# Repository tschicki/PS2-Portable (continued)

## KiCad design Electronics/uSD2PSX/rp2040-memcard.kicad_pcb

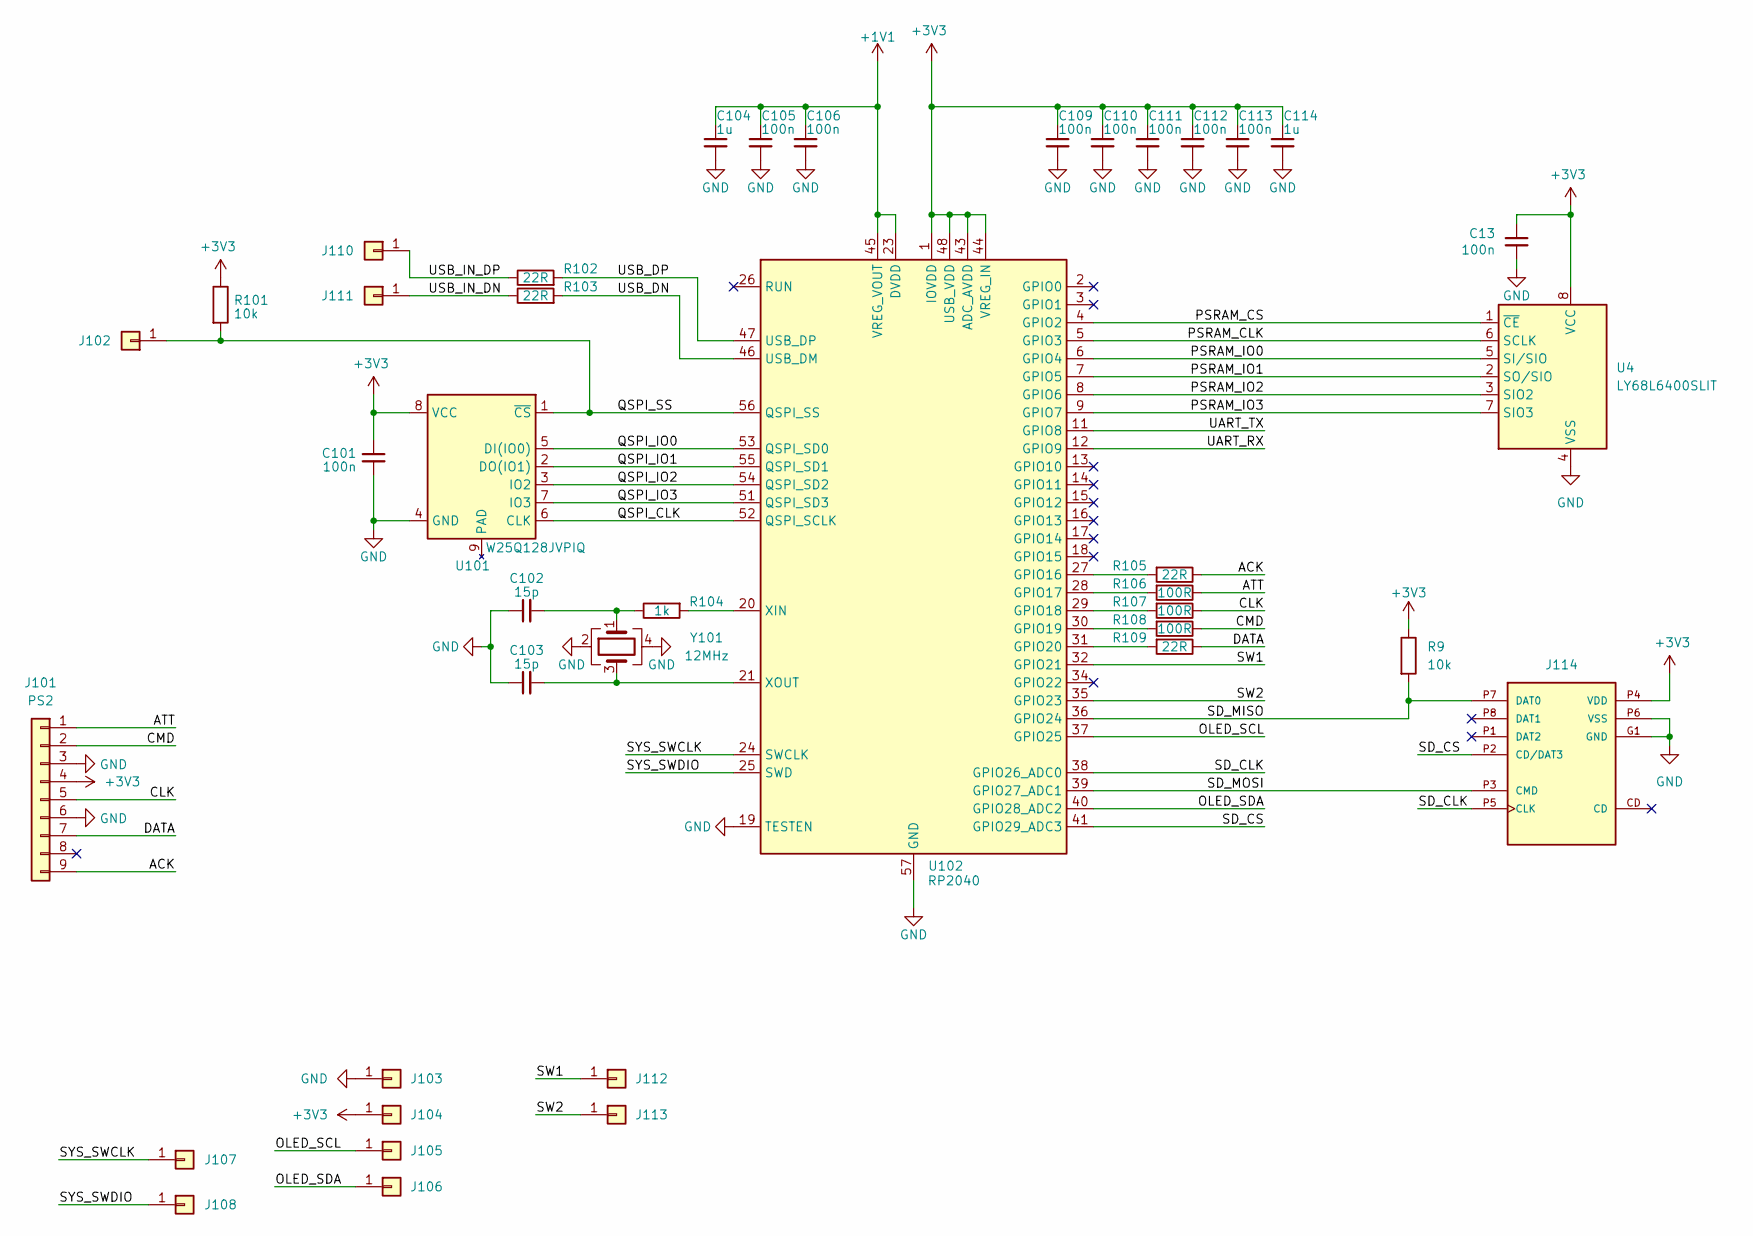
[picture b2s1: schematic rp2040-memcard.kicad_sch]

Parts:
C13, C101, C105, C106, C109, C110, C111, C112, C113: 100n; C_0402_1005Metric; Part Number CC0402KRX7R7BB104
C102, C103: 15p; C_0402_1005Metric; Part Number CC0402JRNPO9BN150
C104, C114: 1u; C_0603_1608Metric; Part Number CC0603KRX7R7BB105
J101: PS2; SD_Pins
J102: BSEL; TestPoint_Pad_D1.0mm
J103, J112: GND; TestPoint_Pad_D1.0mm
J104, J113: 3V3; TestPoint_Pad_D1.0mm
J105: SCL; TestPoint_Pad_D1.0mm
J106: SDA; TestPoint_Pad_D1.0mm
J107: SWC; TestPoint_Pad_D1.0mm
J108: SWD; TestPoint_Pad_D1.0mm
J110: DP; TestPoint_Pad_D1.0mm
J111: DN; TestPoint_Pad_D1.0mm
J114: MEM2085-00-115-00-A_REV0.2; GCT_MEM2085-00-115-00-A_REV0.2; Part Number MEM2085-00-115-00-A
R9, R101: 10k; R_0402_1005Metric; Part Number RC0402JR-0710KL
R102, R103, R105, R109: 22R; R_0402_1005Metric; Part Number RC0402FR-0722RL
R104: 1k; R_0402_1005Metric; Part Number RC0402FR-071KL
R106, R107, R108: 100R; R_0402_1005Metric; Part Number RC0402JR-07100RL
U4: LY68L6400SLIT; IC_W25Q16JVUXIQ_TR; Part Number APS6404L-3SQR-ZR; LCSC C261881
U101: W25Q128JVPIQ; WSON-8-1EP_6x5mm_P1.27mm_EP3.4x4.3mm; Part Number W25Q128JVPIQ
U102: RP2040; QFN-56-1EP_7x7mm_P0.4mm_EP3.2x3.2mm; Part Number RP2040
Y101: 12MHz; Crystal_SMD_3225-4Pin_3.2x2.5mm; Part Number FL1200112

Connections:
+1V1: C104.1, C105.1, C106.1, U102.23 (DVDD), U102.45 (VREG_VOUT), U102.50 (DVDD)
+3V3: C13.1, C101.1, C109.1, C110.1, C111.1, C112.1, C113.1, C114.1, J101.4, J104.1, J114.P4 (VDD), R9.1, R101.1, U4.8 (VCC), U101.8 (VCC), U102.1 (IOVDD), U102.10 (IOVDD), U102.22 (IOVDD), U102.33 (IOVDD), U102.42 (IOVDD), U102.43 (ADC_AVDD), U102.44 (VREG_IN), U102.48 (USB_VDD), U102.49 (IOVDD)
/ACK: J101.9, R105.1
/ATT: J101.1, R106.1
/CLK: J101.5, R107.1
/CMD: J101.2, R108.1
/DATA: J101.7, R109.1
/OLED_SCL: J105.1, U102.37 (GPIO25)
/OLED_SDA: J106.1, U102.40 (GPIO28_ADC2)
/PSRAM_CLK: U4.6 (SCLK), U102.5 (GPIO3)
/PSRAM_CS: U4.1 (~CE), U102.4 (GPIO2)
/PSRAM_IO0: U4.5 (SI/SIO), U102.6 (GPIO4)
/PSRAM_IO1: U4.2 (SO/SIO), U102.7 (GPIO5)
/PSRAM_IO2: U4.3 (SIO2), U102.8 (GPIO6)
/PSRAM_IO3: U4.7 (SIO3), U102.9 (GPIO7)
/QSPI_CLK: U101.6 (CLK), U102.52 (QSPI_SCLK)
/QSPI_IO0: U101.5 (DI(IO0)), U102.53 (QSPI_SD0)
/QSPI_IO1: U101.2 (DO(IO1)), U102.55 (QSPI_SD1)
/QSPI_IO2: U101.3 (IO2), U102.54 (QSPI_SD2)
/QSPI_IO3: U101.7 (IO3), U102.51 (QSPI_SD3)
/QSPI_SS: J102.1, R101.2, U101.1 (~CS), U102.56 (QSPI_SS)
/SD_CLK: J114.P5 (CLK), U102.38 (GPIO26_ADC0)
/SD_CS: J114.P2 (CD/DAT3), U102.41 (GPIO29_ADC3)
/SD_MISO: J114.P7 (DAT0), R9.2, U102.36 (GPIO24)
/SD_MOSI: J114.P3 (CMD), U102.39 (GPIO27_ADC1)
/SW1: J112.1, U102.32 (GPIO21)
/SW2: J113.1, U102.35 (GPIO23)
/SYS_SWCLK: J107.1, U102.24 (SWCLK)
/SYS_SWDIO: J108.1, U102.25 (SWD)
/UART_RX: U102.12 (GPIO9)
/UART_TX: U102.11 (GPIO8)
/USB_DN: R103.2, U102.46 (USB_DM)
/USB_DP: R102.2, U102.47 (USB_DP)
/USB_IN_DN: J111.1, R103.1
/USB_IN_DP: J110.1, R102.1
GND: C13.2, C101.2, C102.1, C103.1, C104.2, C105.2, C106.2, C109.2, C110.2, C111.2, C112.2, C113.2, C114.2, J101.3, J101.6, J103.1, J114.G1 (GND), J114.G2 (GND__1), J114.G3 (GND__2), J114.G4 (GND__3), J114.G5 (GND__4), J114.G6 (GND__5), J114.G7 (GND__6), J114.G8 (GND__7), J114.G9 (GND__8), J114.G10 (GND__9), J114.P6 (VSS), U4.4 (VSS), U101.4 (GND), U102.19 (TESTEN), U102.57 (GND), Y101.2, Y101.4
unnamed: C102.2, R104.1, Y101.1
unnamed: R105.2, U102.27 (GPIO16)
unnamed: R106.2, U102.28 (GPIO17)
unnamed: R107.2, U102.29 (GPIO18)
unnamed: R108.2, U102.30 (GPIO19)
unnamed: R109.2, U102.31 (GPIO20)
unnamed: R104.2, U102.20 (XIN)
unnamed: C103.2, U102.21 (XOUT), Y101.3

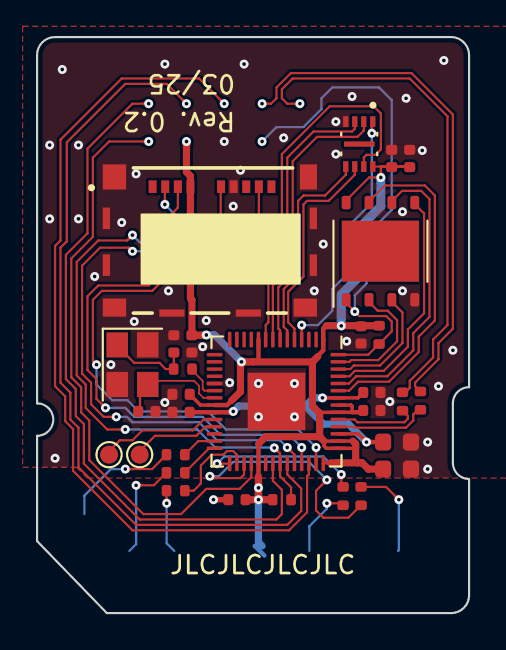
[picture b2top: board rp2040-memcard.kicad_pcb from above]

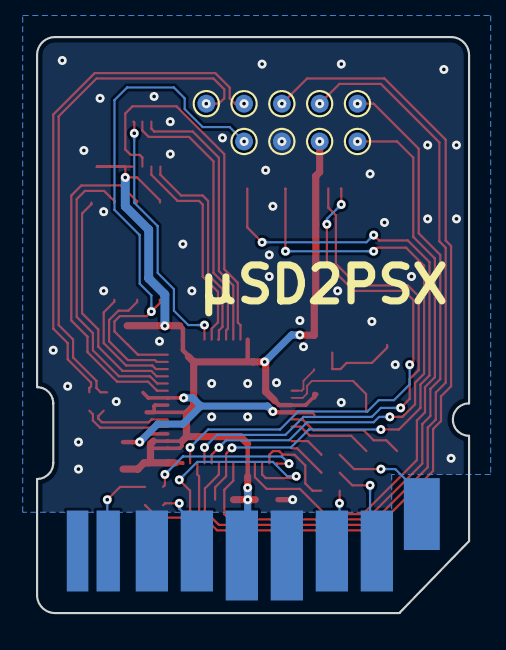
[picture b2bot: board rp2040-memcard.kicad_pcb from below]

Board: 2 copper layers, 24.0 x 32.0 mm, 40 parts (10 on the bottom side), 42 nets.

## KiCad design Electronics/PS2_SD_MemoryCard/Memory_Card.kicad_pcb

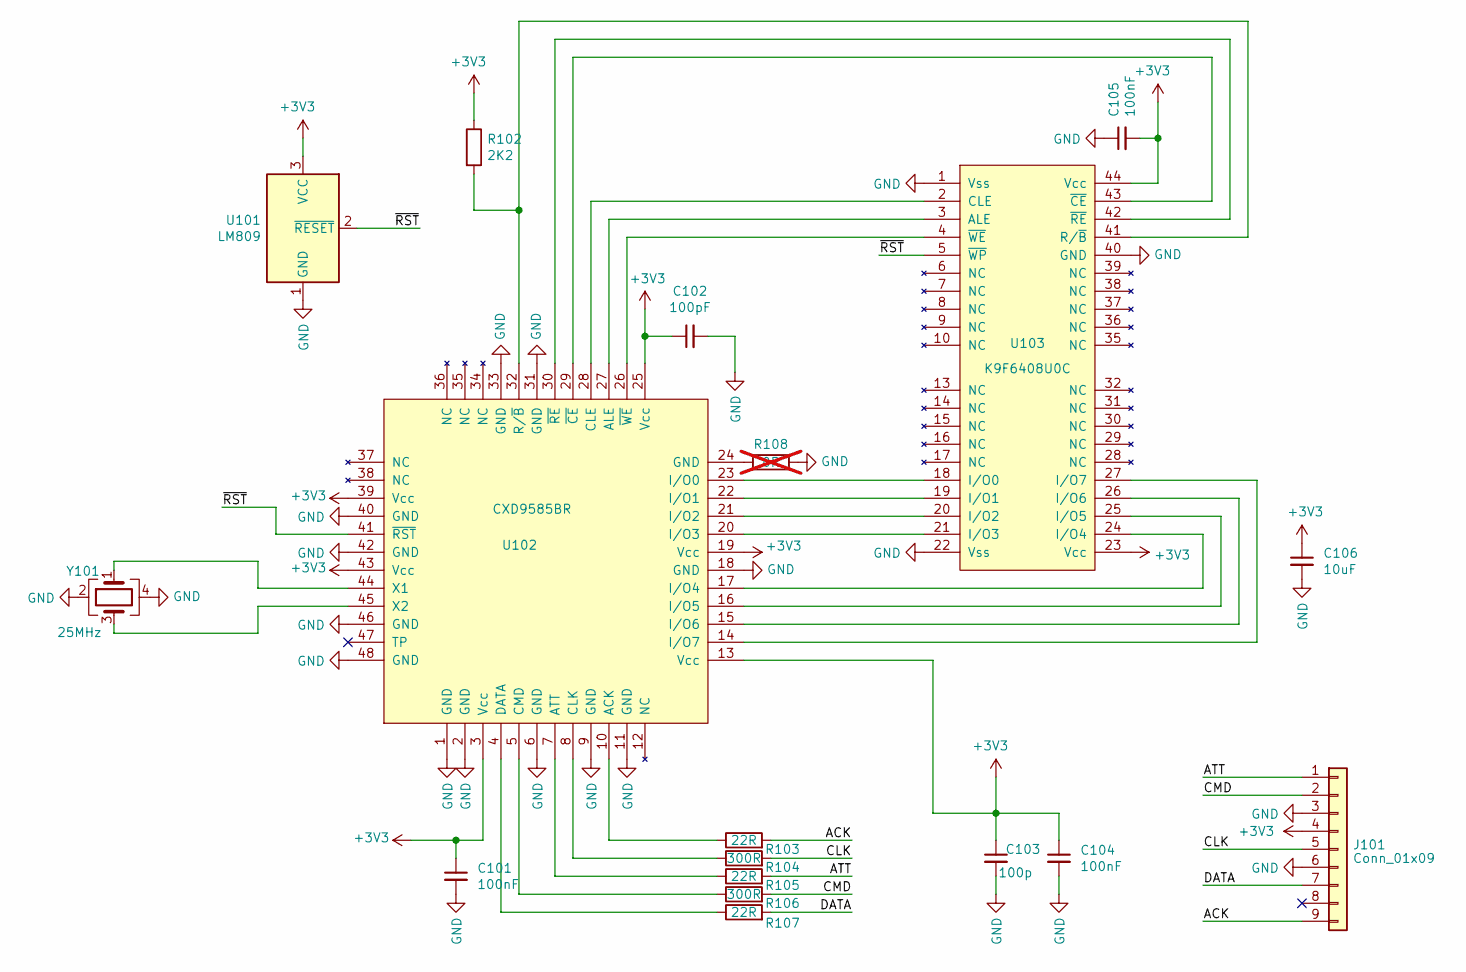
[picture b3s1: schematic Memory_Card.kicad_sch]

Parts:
C101, C104, C105: 100nF; C_0402_1005Metric; Part Number CC0402KRX7R7BB104
C102: 100pF; C_0402_1005Metric; Part Number CC0402KRX7R9BB101
C103: 100p; C_0402_1005Metric; Part Number CC0402KRX7R9BB101
C106: 10uF; C_0805_2012Metric; Part Number 885012107014
J101: Conn_01x09; SD_Pins
R102: 2K2; R_0402_1005Metric; Part Number RC0402FR-072K2L
R103, R105, R107: 22R; R_0402_1005Metric; Part Number RC0402FR-0722RL
R104, R106: 300R; R_0402_1005Metric; Part Number RC0402JR-07300RL
R108: 0R; R_0402_1005Metric; Part Number RC0402JR-130RL; not fitted
U101: LM809; SOT-23; Part Number LM809M3-2.63/NOPB
U102: CXD9585BR; LQFP-48_7x7mm_P0.5mm; Part Number Get off board
U103: K9F6408U0C; TSOP-II-44_10.16x18.41mm_P0.8mm; Part Number Get off board
Y101: 25MHz; Crystal_SMD_2016-4Pin_2.0x1.6mm; Part Number 402F2501XIAR

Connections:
+3V3: C101.1, C102.1, C103.1, C104.1, C105.2, C106.1, J101.4, R102.1, U101.3 (VCC), U102.3 (Vcc), U102.13 (Vcc), U102.19 (Vcc), U102.25 (Vcc), U102.39 (Vcc), U102.43 (Vcc), U103.23 (Vcc), U103.44 (Vcc)
/ACK: J101.9, R103.2
/ATT: J101.1, R105.2
/CLK: J101.5, R104.2
/CMD: J101.2, R106.2
/DATA: J101.7, R107.2
/~RST: U101.2 (~RESET), U102.41 (~RST), U103.5 (~WP)
GND: C101.2, C102.2, C103.2, C104.2, C105.1, C106.2, J101.3, J101.6, R108.2, U101.1 (GND), U102.1 (GND), U102.2 (GND), U102.6 (GND), U102.9 (GND), U102.11 (GND), U102.18 (GND), U102.31 (GND), U102.33 (GND), U102.40 (GND), U102.42 (GND), U102.46 (GND), U102.48 (GND), U103.1 (Vss), U103.22 (Vss), U103.40 (GND), Y101.2, Y101.4
unnamed: R108.1, U102.24 (GND)
unnamed: R103.1, U102.10 (ACK)
unnamed: U102.27 (ALE), U103.3 (ALE)
unnamed: R105.1, U102.7 (ATT)
unnamed: U102.28 (CLE), U103.2 (CLE)
unnamed: R104.1, U102.8 (CLK)
unnamed: R106.1, U102.5 (CMD)
unnamed: R107.1, U102.4 (DATA)
unnamed: U102.23 (I/O0), U103.18 (I/O0)
unnamed: U102.22 (I/O1), U103.19 (I/O1)
unnamed: U102.21 (I/O2), U103.20 (I/O2)
unnamed: U102.20 (I/O3), U103.21 (I/O3)
unnamed: U102.17 (I/O4), U103.24 (I/O4)
unnamed: U102.16 (I/O5), U103.25 (I/O5)
unnamed: U102.15 (I/O6), U103.26 (I/O6)
unnamed: U102.14 (I/O7), U103.27 (I/O7)
unnamed: R102.2, U102.32 (R/~B), U103.41 (R/~B)
unnamed: U102.44 (X1), Y101.1
unnamed: U102.45 (X2), Y101.3
unnamed: U102.29 (~CE), U103.43 (~CE)
unnamed: U102.30 (~RE), U103.42 (~RE)
unnamed: U102.26 (~WE), U103.4 (~WE)

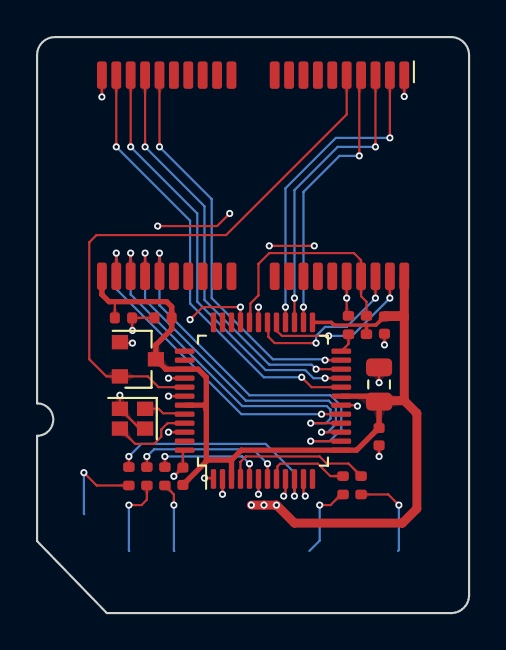
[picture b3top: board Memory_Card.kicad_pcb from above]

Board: 2 copper layers, 24.0 x 32.0 mm, 18 parts (1 on the bottom side), 30 nets.

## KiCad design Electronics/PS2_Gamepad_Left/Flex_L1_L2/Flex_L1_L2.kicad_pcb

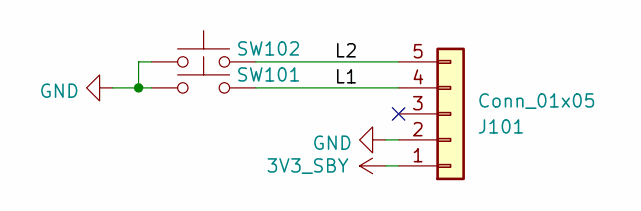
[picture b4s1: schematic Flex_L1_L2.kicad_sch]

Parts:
J101: Conn_01x05; 5034800540_FFC
SW101, SW102: SW; SW_KSC222J_LFS; Part Number KSC222J_LFS

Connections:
3V3_SBY: J101.1
/L1: J101.4, SW101.2
/L2: J101.5, SW102.2
GND: J101.2, SW101.1, SW102.1

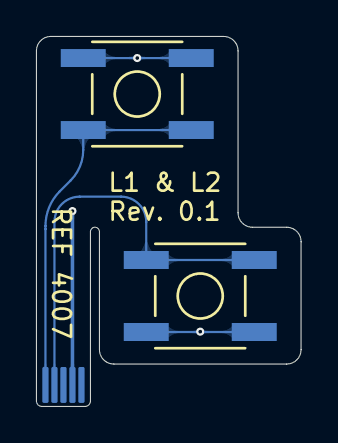
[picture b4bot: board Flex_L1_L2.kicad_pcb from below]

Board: 2 copper layers, 14.7 x 20.6 mm, 3 parts (3 on the bottom side), 3 nets.

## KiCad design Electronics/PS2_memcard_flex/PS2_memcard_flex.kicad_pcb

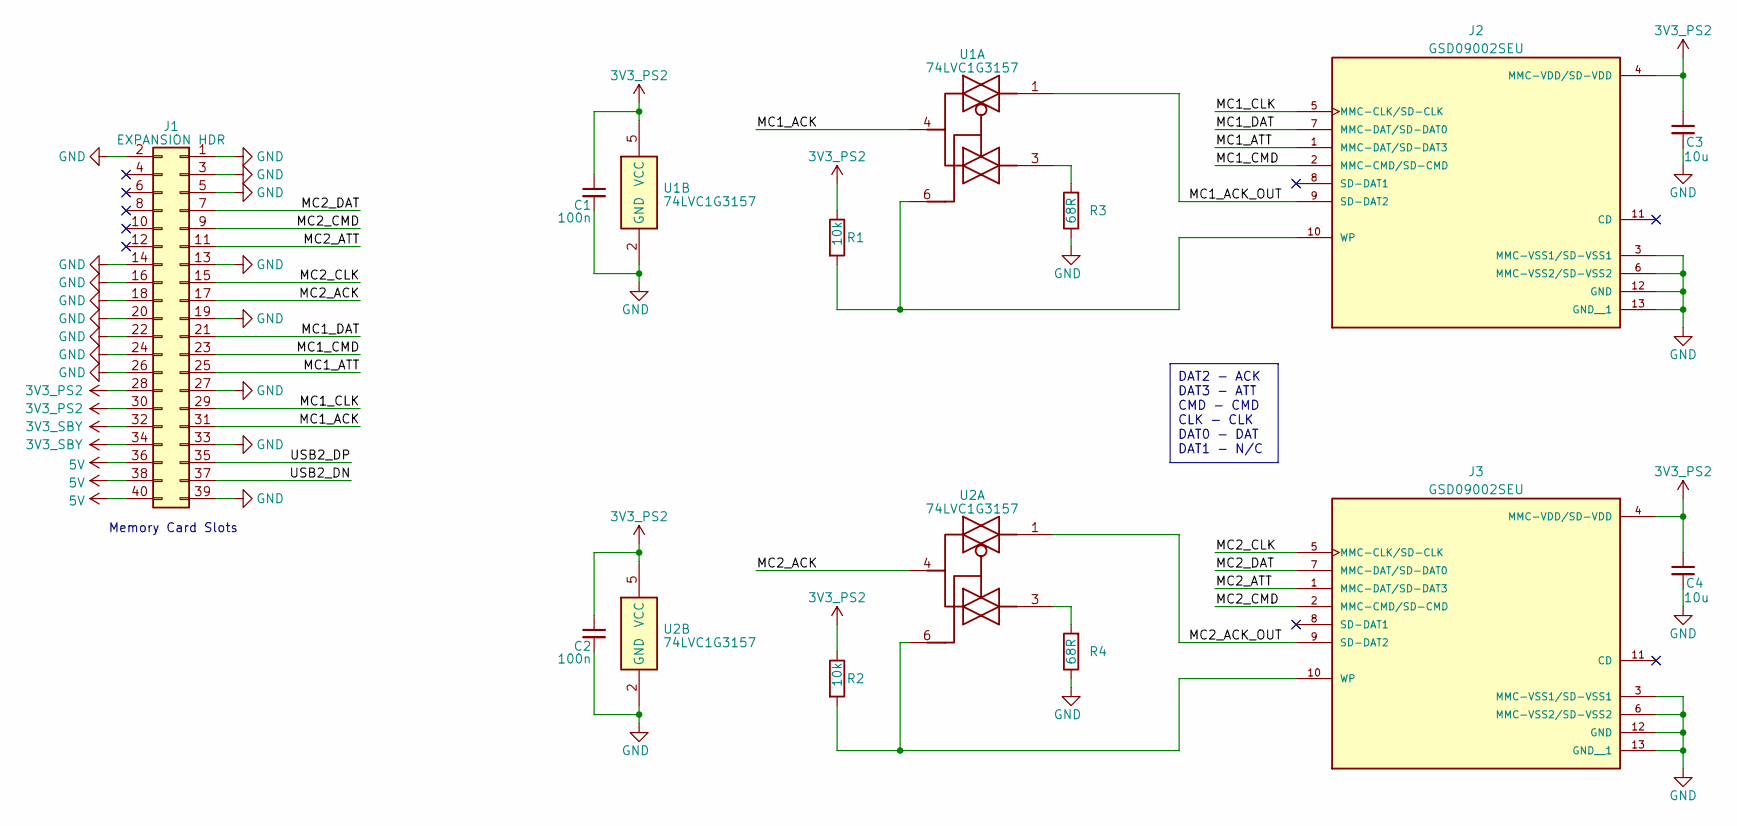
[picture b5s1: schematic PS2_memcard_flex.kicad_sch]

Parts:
C1, C2: 100n; C_0402_1005Metric; Part Number CC0402KRX7R7BB104
C3, C4: 10u; C_0805_2012Metric; Part Number TMK212BBJ106MGHT
J1: EXPANSION HDR; DF40C-40DP-0.4V; Part Number DF40C-40DP-0.4V(51)
J2, J3: GSD09002SEU; AMPHENOL_GSD09002SEU; Part Number GSD09002SEU
R1, R2: 10k; R_0402_1005Metric; Part Number RC0402JR-0710KL
R3, R4: 68R; R_0402_1005Metric; Part Number RC0402FR-0768RL
U1, U2: 74LVC1G3157; SOT-363_SC-70-6; Part Number 74LVC1G3157GW,125

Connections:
3V3_PS2: C1.1, C2.1, C3.1, C4.1, J1.28, J1.30, J2.4 (MMC-VDD/SD-VDD), J3.4 (MMC-VDD/SD-VDD), R1.1, R2.1, U1.5 (VCC), U2.5 (VCC)
3V3_SBY: J1.32, J1.34
5V: J1.36, J1.38, J1.40
/MC1_ACK: J1.31, U1.4
/MC1_ACK_OUT: J2.9 (SD-DAT2), U1.1
/MC1_ATT: J1.25, J2.1 (MMC-DAT/SD-DAT3)
/MC1_CLK: J1.29, J2.5 (MMC-CLK/SD-CLK)
/MC1_CMD: J1.23, J2.2 (MMC-CMD/SD-CMD)
/MC1_DAT: J1.21, J2.7 (MMC-DAT/SD-DAT0)
/MC2_ACK: J1.17, U2.4
/MC2_ACK_OUT: J3.9 (SD-DAT2), U2.1
/MC2_ATT: J1.11, J3.1 (MMC-DAT/SD-DAT3)
/MC2_CLK: J1.15, J3.5 (MMC-CLK/SD-CLK)
/MC2_CMD: J1.9, J3.2 (MMC-CMD/SD-CMD)
/MC2_DAT: J1.7, J3.7 (MMC-DAT/SD-DAT0)
/USB2_DN: J1.37
/USB2_DP: J1.35
GND: C1.2, C2.2, C3.2, C4.2, J1.1, J1.2, J1.3, J1.5, J1.13, J1.14, J1.16, J1.18, J1.19, J1.20, J1.22, J1.24, J1.26, J1.27, J1.33, J1.39, J2.3 (MMC-VSS1/SD-VSS1), J2.6 (MMC-VSS2/SD-VSS2), J2.12 (GND), J2.13 (GND__1), J3.3 (MMC-VSS1/SD-VSS1), J3.6 (MMC-VSS2/SD-VSS2), J3.12 (GND), J3.13 (GND__1), R3.1, R4.1, U1.2 (GND), U2.2 (GND)
unnamed: J2.10 (WP), R1.2, U1.6
unnamed: J3.10 (WP), R2.2, U2.6
unnamed: R3.2, U1.3
unnamed: R4.2, U2.3

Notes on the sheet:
DAT2 - ACK DAT3 - ATT CMD - CMD CLK - CLK DAT0 - DAT DAT1 - N/C
Memory Card Slots

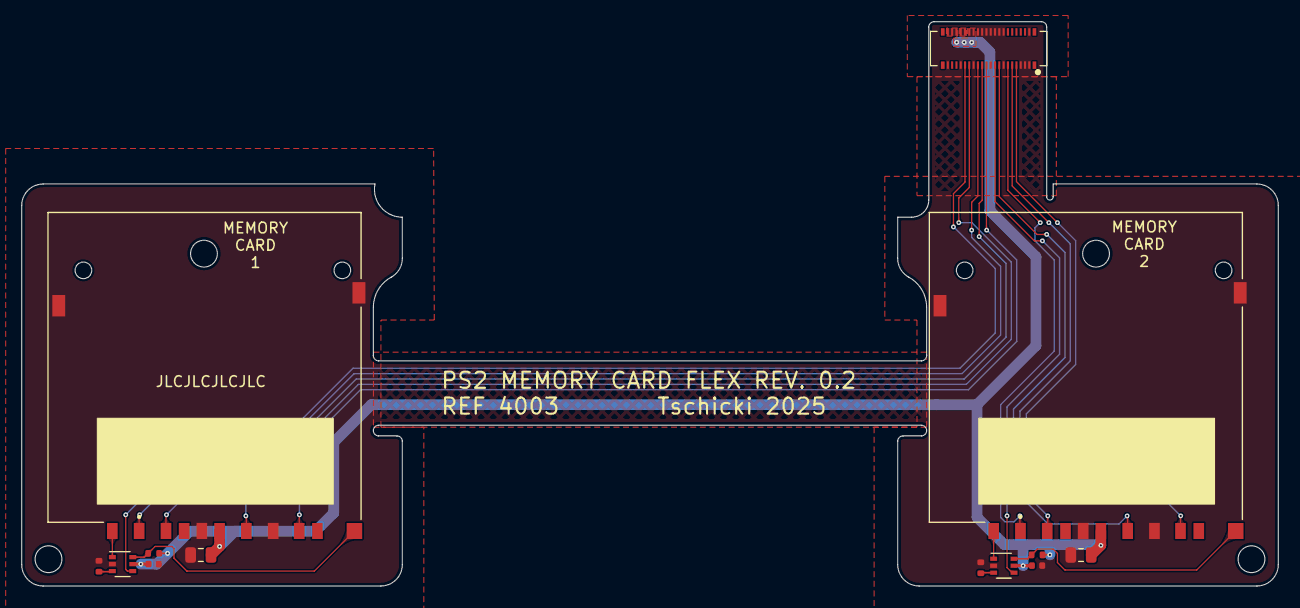
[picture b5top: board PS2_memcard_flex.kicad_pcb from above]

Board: 2 copper layers, 117.2 x 52.6 mm, 13 parts (0 on the bottom side), 20 nets.

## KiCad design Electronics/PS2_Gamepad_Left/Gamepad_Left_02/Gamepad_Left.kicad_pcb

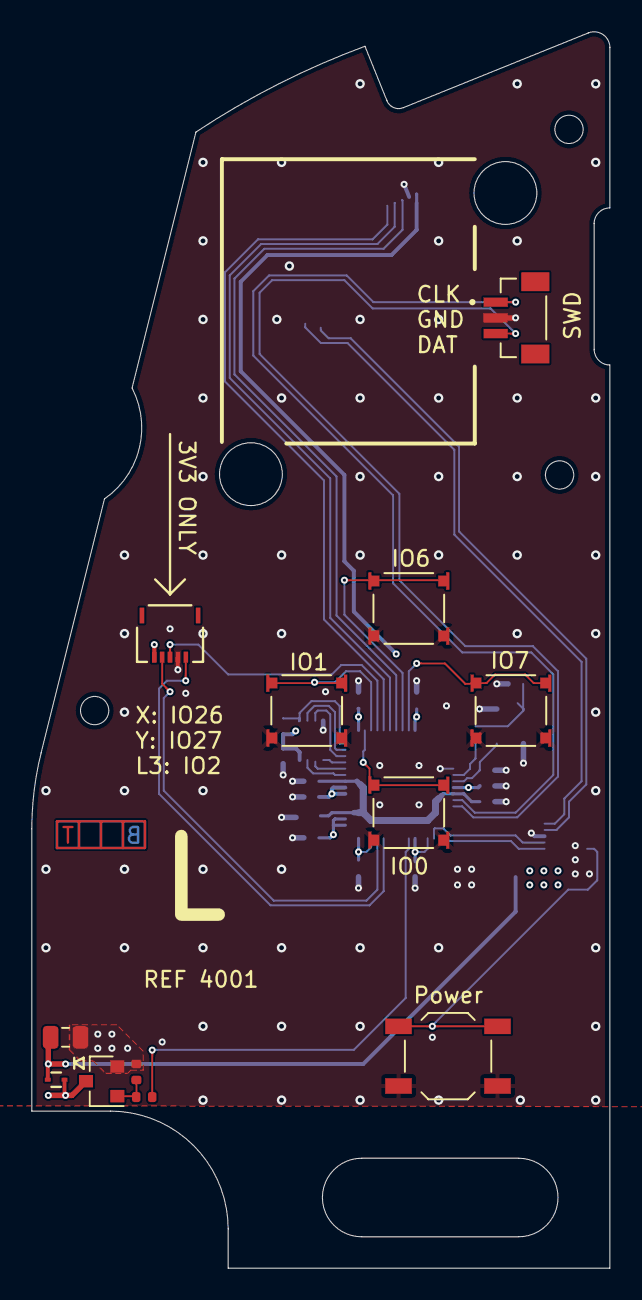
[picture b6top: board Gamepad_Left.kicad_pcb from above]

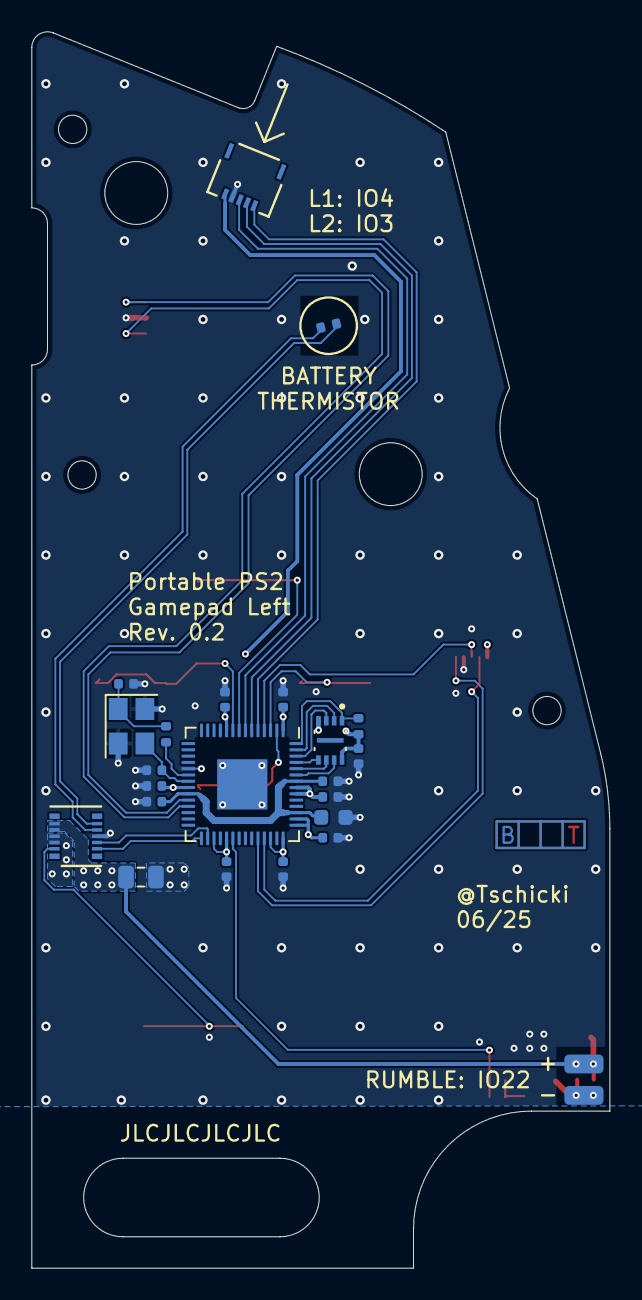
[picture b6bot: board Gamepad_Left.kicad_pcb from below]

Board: 4 copper layers, 36.8 x 78.7 mm, 35 parts (23 on the bottom side), 32 nets.

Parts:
C101, C105, C106, C107, C109, C110, C111, C112, C113, C114: 100n; C_0402_1005Metric
C102, C103: 15p; C_0402_1005Metric
C104: 1u; C_0603_1608Metric
C108, C115: 4u7; C_0805_2012Metric
D101: D_Schottky; SOD-923_0P6X0P85_ONS
J101: DEBUG_SWD; JST_BM03B-SRSS-TB_LF__SN_
J102: GAMEPAD LEFT; DF40C-10DP-0.4V51_HIR
J103, J116: Conn_01x05_MountingPin; CON_5034800540_MOL
J104: Motor; rumble_dual_solder_pad
Q101: BSS138; SOT-23
R101, R103: 10k; R_0402_1005Metric
R102, R104: 1k; R_0402_1005Metric
SW101, SW102, SW103, SW104: SW; SW_TL3315NF100Q
SW114: SW; SW_SPST_TL3342
TH101: 10k/3435K; R_0402_1005Metric
U101: W25Q16JVUXIQ; IC_W25Q16JVUXIQ_TR
U102: RP2040; QFN-56-1EP_7x7mm_P0.4mm_EP3.2x3.2mm
Y101: 12MHz; Crystal_SMD_3225-4Pin_3.2x2.5mm

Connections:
3V3_SBY: C101.1, C107.1, C108.1, C109.1, C110.1, C111.1, C112.1, C113.1, C114.1, C115.1, D101.1 (K), J102.7, J102.9, J103.5, J104.1, J116.5, R101.1, U101.8 (VCC), U102.1 (IOVDD), U102.10 (IOVDD), U102.22 (IOVDD), U102.31 (GPIO20), U102.33 (IOVDD), U102.40 (GPIO28_ADC2), U102.42 (IOVDD), U102.43 (ADC_AVDD), U102.44 (VREG_IN), U102.48 (USB_VDD), U102.49 (IOVDD)
+1V1: C104.1, C105.1, C106.1, U102.23 (DVDD), U102.45 (VREG_VOUT), U102.50 (DVDD)
/AUX_I2C_SCL: J102.4, U102.30 (GPIO19)
/AUX_I2C_SDA: J102.2, U102.29 (GPIO18)
/CS: R101.2, U101.1 (~CS), U102.56 (QSPI_SS)
/Down: SW103.1, U102.2 (GPIO0)
/IO0: U101.5 (DI(IO0)), U102.53 (QSPI_SD0)
/IO1: U101.2 (DO(IO1)), U102.55 (QSPI_SD1)
/IO2: U101.3 (IO2), U102.54 (QSPI_SD2)
/IO3: U101.7 (IO3), U102.51 (QSPI_SD3)
/L1: J103.2, U102.6 (GPIO4)
/L2: J103.1, U102.5 (GPIO3)
/L3: J116.3, U102.4 (GPIO2)
/Left: SW101.1, U102.3 (GPIO1)
/MEM_CLK: U101.6 (CLK), U102.52 (QSPI_SCLK)
/PWM_Rumble: R102.1, U102.34 (GPIO22)
/Reserved: J103.3, U102.7 (GPIO5)
/Right: SW104.1, U102.9 (GPIO7)
/SWCLK: J101.1, U102.24 (SWCLK)
/SWDIO: J101.3, U102.25 (SWD)
/SYS_PWR_BTN: J102.1, SW114.1
/TS_+: J102.8, TH101.2
/TS_-: J102.10, TH101.1
/Up: SW102.1, U102.8 (GPIO6)
/X: J116.1, U102.38 (GPIO26_ADC0)
/XI: C103.2, U102.21 (XOUT), Y101.3
/XO: R104.2, U102.20 (XIN)
/Y: J116.4, U102.39 (GPIO27_ADC1)
GND: C101.2, C102.1, C103.1, C104.2, C105.2, C106.2, C107.2, C108.2, C109.2, C110.2, C111.2, C112.2, C113.2, C114.2, C115.2, J101.2, J102.3, J102.5, J102.6, J103.4, J116.2, Q101.2 (S), R103.2, SW101.2, SW102.2, SW103.2, SW104.2, SW114.2, U101.4 (GND), U102.19 (TESTEN), U102.57 (GND), Y101.2, Y101.4
unnamed: C102.2, R104.1, Y101.1
unnamed: D101.2 (A), J104.2, Q101.3 (D)
unnamed: Q101.1 (G), R102.2, R103.1

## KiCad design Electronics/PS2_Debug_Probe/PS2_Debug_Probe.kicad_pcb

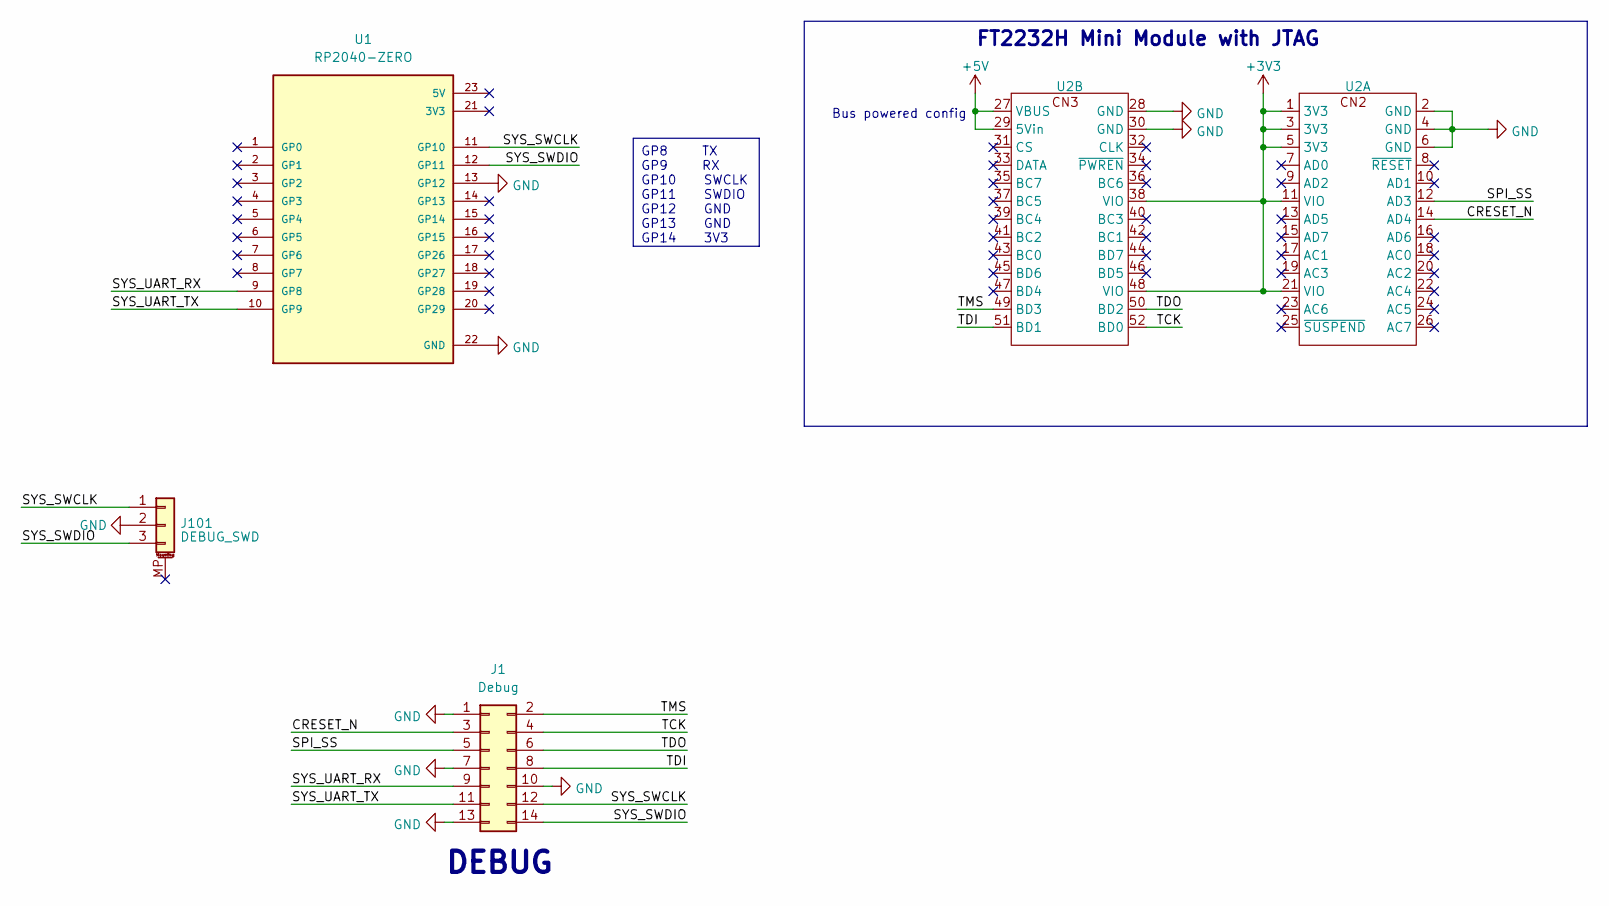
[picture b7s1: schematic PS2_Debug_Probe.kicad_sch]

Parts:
J1: Debug; FTSH-107-01-F-DV-K-P-TR; Part Number FTSH-107-01-F-DV-K-P-TR
J101: DEBUG_SWD; JST_SM03B-SRSS-TB(LF)(SN); Part Number SM03B-SRSS-TB
U1: RP2040-ZERO; MODULE_RP2040-ZERO; PARTREV NA
U2: FT2232H_mini_module_jtag

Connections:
+3V3: U2.1 (3V3), U2.3 (3V3), U2.5 (3V3), U2.11 (VIO), U2.21 (VIO), U2.38 (VIO), U2.48 (VIO)
+5V: U2.27 (VBUS), U2.29 (5Vin)
/CRESET_N: J1.3, U2.14 (AD4)
/SPI_SS: J1.5, U2.12 (AD3)
/SYS_SWCLK: J1.12, J101.1, U1.11 (GP10)
/SYS_SWDIO: J1.14, J101.3, U1.12 (GP11)
/SYS_UART_RX: J1.9, U1.9 (GP8)
/SYS_UART_TX: J1.11, U1.10 (GP9)
/TCK: J1.4, U2.52 (BD0)
/TDI: J1.8, U2.51 (BD1)
/TDO: J1.6, U2.50 (BD2)
/TMS: J1.2, U2.49 (BD3)
GND: J1.1, J1.7, J1.10, J1.13, J101.2, U1.13 (GP12), U1.22 (GND), U2.2 (GND), U2.4 (GND), U2.6 (GND), U2.28 (GND), U2.30 (GND)

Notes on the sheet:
GP8 TX GP9 RX GP10 SWCLK GP11 SWDIO GP12 GND GP13 GND GP14 3V3
FT2232H Mini Module with JTAG
Bus powered config
DEBUG

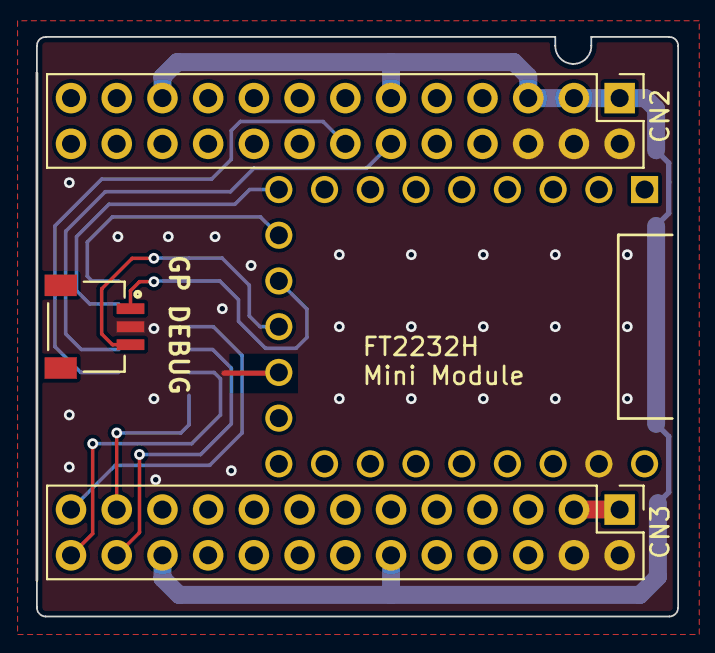
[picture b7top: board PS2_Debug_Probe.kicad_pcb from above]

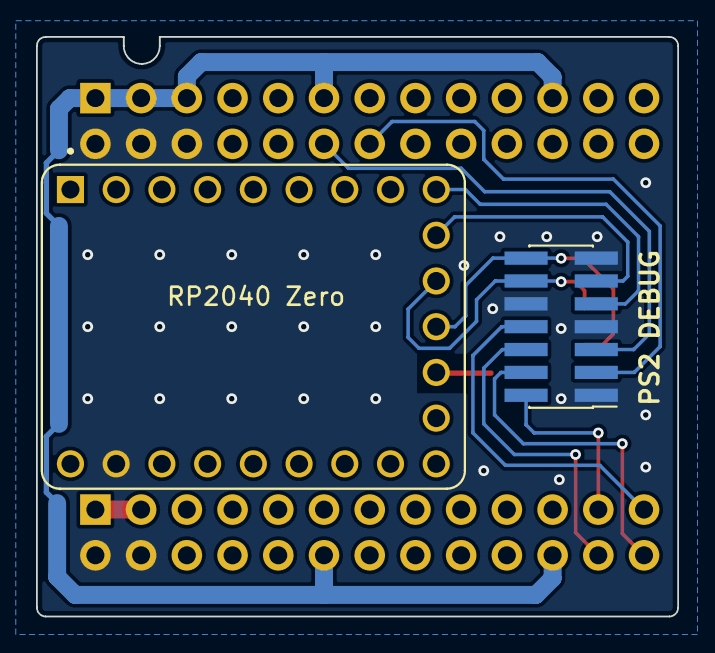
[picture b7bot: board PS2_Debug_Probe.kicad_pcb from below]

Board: 2 copper layers, 35.6 x 32.2 mm, 4 parts (2 on the bottom side), 13 nets.

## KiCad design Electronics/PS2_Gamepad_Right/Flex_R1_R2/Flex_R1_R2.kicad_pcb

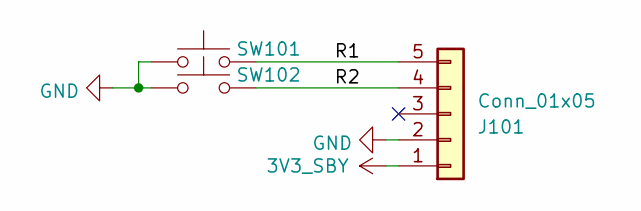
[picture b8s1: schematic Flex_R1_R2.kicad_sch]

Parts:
J101: Conn_01x05; 5034800540_FFC
SW101, SW102: SW; SW_KSC222J_LFS; Part Number KSC222J_LFS

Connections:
3V3_SBY: J101.1
/R1: J101.5, SW101.2
/R2: J101.4, SW102.2
GND: J101.2, SW101.1, SW102.1

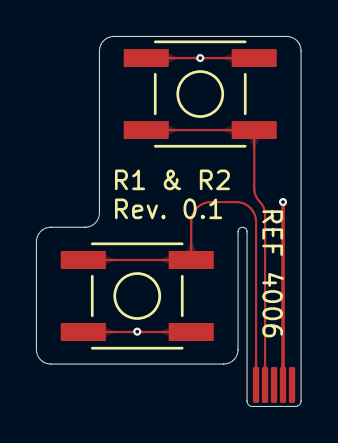
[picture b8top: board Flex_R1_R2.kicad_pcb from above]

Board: 2 copper layers, 14.7 x 20.6 mm, 3 parts (0 on the bottom side), 3 nets.

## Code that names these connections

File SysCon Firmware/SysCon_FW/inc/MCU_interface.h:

#ifndef MCU_interface_h
#define MCU_interface_h

#include <stdint.h>
#include <stdio.h>
#include <string.h>
#include <math.h>
#include <stdlib.h>


#include "pico/stdlib.h"
#include "pico/stdio/driver.h"
#include "hardware/i2c.h"
#include "hardware/spi.h"
#include "pico/multicore.h"
#include "hardware/pwm.h"
#include "hardware/adc.h"
#include "hardware/flash.h"
#include "hardware/resets.h"
#include "hardware/clocks.h"
#include "hardware/pio.h"
#include "hardware/watchdog.h"

#include "Error_Codes.h"
#include "system_states.h"

//----------------------------------------------------------------------------------------------------------------------------------------------------------------------
/*Defines for mainboard bringup, BE VERY CAREFUL!*/
//#define MFG_STEP_1    /*will configure the firmware to flash the STUSB4500 config upon long-press of the power button, then halt*/
//#define MFG_STEP_2    /*will configure the firmware to enable operation without batteries*/
//#define MFG_STEP_3    /*will configure the firmware to flash the MAX17320 NVM config -> do this only once or twice, very limited write cycles!*/
//----------------------------------------------------------------------------------------------------------------------------------------------------------------------


/*set the firmware version here*/
#define FW_VERSION_MAJOR    1
#define FW_VERSION_MINOR    4
/*Debug print for various functions*/
//#define BQ_DEBUG      /*will enable UART debug print for the BQ25792*/
//#define MAX_DEBUG     /*will enable UART debug print for the MAX17320*/
//#define I2C_DEBUG     /*will enable UART debug print for all I2C communication*/
//#define STUSB_DEBUG   /*will enable UART debug print for the STUSB4500*/
//#define STATE_DEBUG   /*will enable UART debug print for the main state machine*/
#define BLOCK_T20_JTAG  /*will block flashing the FPGA via JTAG during runtime*/


/*no touch zone*/
#if defined(MFG_STEP_1)
    #define DEBUG_WRITE_STUSB_NVM
    #define DEBUG_IGNORE_MAX
    #define BLOCK_CHARGE
    #if defined(MFG_STEP_2) || defined(MFG_STEP_3)
    _Static_assert(0, "Only one MFG step at a time!");
    #endif
#endif

#if defined(MFG_STEP_2)
    #define DEBUG_IGNORE_MAX
    #define BLOCK_CHARGE
    #if defined(MFG_STEP_1) || defined(MFG_STEP_3)
    _Static_assert(0, "Only one MFG step at a time!");
    #endif
#endif

#if defined(MFG_STEP_3)
    #define DEBUG_FLASH_MAX_NVM
    #define BLOCK_CHARGE
    #if defined(MFG_STEP_1) || defined(MFG_STEP_2)
    _Static_assert(0, "Only one MFG step at a time!");
    #endif
#else
    /*the watchdog could trigger while the MAX17320 NVM is updating, that's why we turn it off for this step*/
    #define WATCHDOG_EN
    #define WATCHDOG_TIMEOUT       10000 //ms
#endif

/*general defines*/
#define ENABLE              1
#define DISABLE             0
#define OK                  0
#define NOK                 1
#define TRUE                1
#define FALSE               0
#define ERROR               2
#define I2C_SUCCESS         0
#define I2C_FAIL            1
/*Power management I2C definitions*/
#define PRW_I2C             i2c0
#define PWR_I2C_BAUD_RATE       400000
#define PWR_I2C_SDA_PIN     20
#define PWR_I2C_SCL_PIN     21
/*Gamepad I2C definitions*/
#define GAMEPAD_I2C             i2c1
#define GAMEPAD_I2C_BAUD_RATE   400000
#define GAMEPAD_I2C_SDA_PIN     18
#define GAMEPAD_I2C_SCL_PIN     19
/*Debug UART definitions*/
#define UART                uart0
#define UART_BAUD_RATE      115200
#define UART_TX_PIN         0
#define UART_RX_PIN         1
/*Gamepad SPI definitions*/
#define GAMEPAD_SPI         spi0
#define GAMEPAD_ACK_PIN     6
#define GAMEPAD_SCK_PIN     4
#define GAMEPAD_DATA_PIN    3
#define GAMEPAD_CMD_PIN     2
#define GAMEPAD_ATT_PIN     5
/*FPGA SPI definitions*/
#define FPGA_SPI            spi1
#define FPGA_SPI_BAUDRATE   25000000
#define FPGA_SCK_PIN        10
#define FPGA_RX_PIN         12
#define FPGA_TX_PIN         11
#define T_CRESET_MS         1
#define T_DMIN_MS           1

/*SysCon pin states to set*/
#define SYSPIN_HIGH         1  
#define SYSPIN_LOW          0
#define SYSPIN_HIZ          2
/*SysCon pin configuration defines*/
#define SYSPIN_NOPULL       0
#define SYSPIN_PULLUP       1
#define SYSPIN_PULLDOWN     3
#define SYSPIN_INPUT        4
#define SYSPIN_OUTPUT       5
#define SYSPIN_OUT_OD       6

#define POWER_GOOD_PIN      26


/*SYSCON used pin definitions*/
typedef enum syscone_pins_e
{
    PIN_CHARGE_EN = 0,    
    PIN_DCDC_PG,      
    PIN_POWERBTN,     
    PIN_PS2_RESET,    
    PIN_PS2_LED_GREEN,
    PIN_PS2_LED_RED,  
    PIN_SYS_FORCE_ON, 
    PIN_DCDC_EN,         
    PIN_GAMEPAD_ACK,      
    PIN_HP_DETECT,
    PIN_T20_CRESET,
    PIN_T20_CDONE,
    PIN_T20_CE0,
    PIN_T20_CE1,

    SYSCON_PINCOUNT,
}syscon_pins_t;

struct io_location
{
    uint8_t io_pin;
    uint8_t reset_state;
    uint8_t pin_mode;
    uint8_t pull_mode;
    uint8_t pin_speed;
    uint8_t drive_strength;
};

struct SysCon_Pins
{
    struct io_location pin[SYSCON_PINCOUNT]; 
};


void i2c_interface_init(i2c_inst_t *hi2c, uint8_t SDA_Pin, uint8_t SCL_Pin, uint32_t baudrate);
void spi_interface_init(spi_inst_t *spi, uint8_t tx_pin, uint8_t rx_pin, uint8_t clk_pin, uint32_t baudrate);

void SystemClock_Config(void);

void MX_UART_Init(uart_inst_t *huart0);
static void init_gpio_struct(struct SysCon_Pins *io);
static void init_gpio_configs(struct SysCon_Pins *io);
void MX_GPIO_Init(struct SysCon_Pins *io);


syscon_error_t i2c_read(i2c_inst_t *interface, uint8_t slave_addr, uint8_t reg_addr, uint8_t *reg_data, uint32_t len);
syscon_error_t i2c_read_no_regs(i2c_inst_t *interface, uint8_t slave_addr, uint8_t *reg_data, uint32_t len);
syscon_error_t i2c_write(i2c_inst_t *interface, uint8_t slave_addr, uint8_t reg_addr, uint8_t *reg_data, uint32_t len);
syscon_error_t spi_write(spi_inst_t *spi, uint8_t len, uint8_t *frame);
syscon_error_t spi_read_write(spi_inst_t *spi, uint8_t *source, uint8_t *dest, uint8_t len);

void delay_ms(uint32_t period);
void delay_us(uint64_t period);
void error_handler(int8_t result);
void sys_set_pin(struct io_location io, uint8_t pin_state);
uint8_t sys_get_pin(struct io_location io);

#endif

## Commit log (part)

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2025-11-29 Release files
2025-11-29 re-export mainboard BOM
2025-12-19 implement magh-autodetect feature; various corrections in the docs based on feedback
2025-12-29 fix distorted video output for MAGH 9 setting; remove unused MAGH 8 setting from menu
2026-04-04 Add a version of the top housing with design supports on some features for more consistent print results
2026-06-21 correct part number of uSD2PSX SPI flash
2026-06-23 Update part number of crystal Y1502 on REF4000
